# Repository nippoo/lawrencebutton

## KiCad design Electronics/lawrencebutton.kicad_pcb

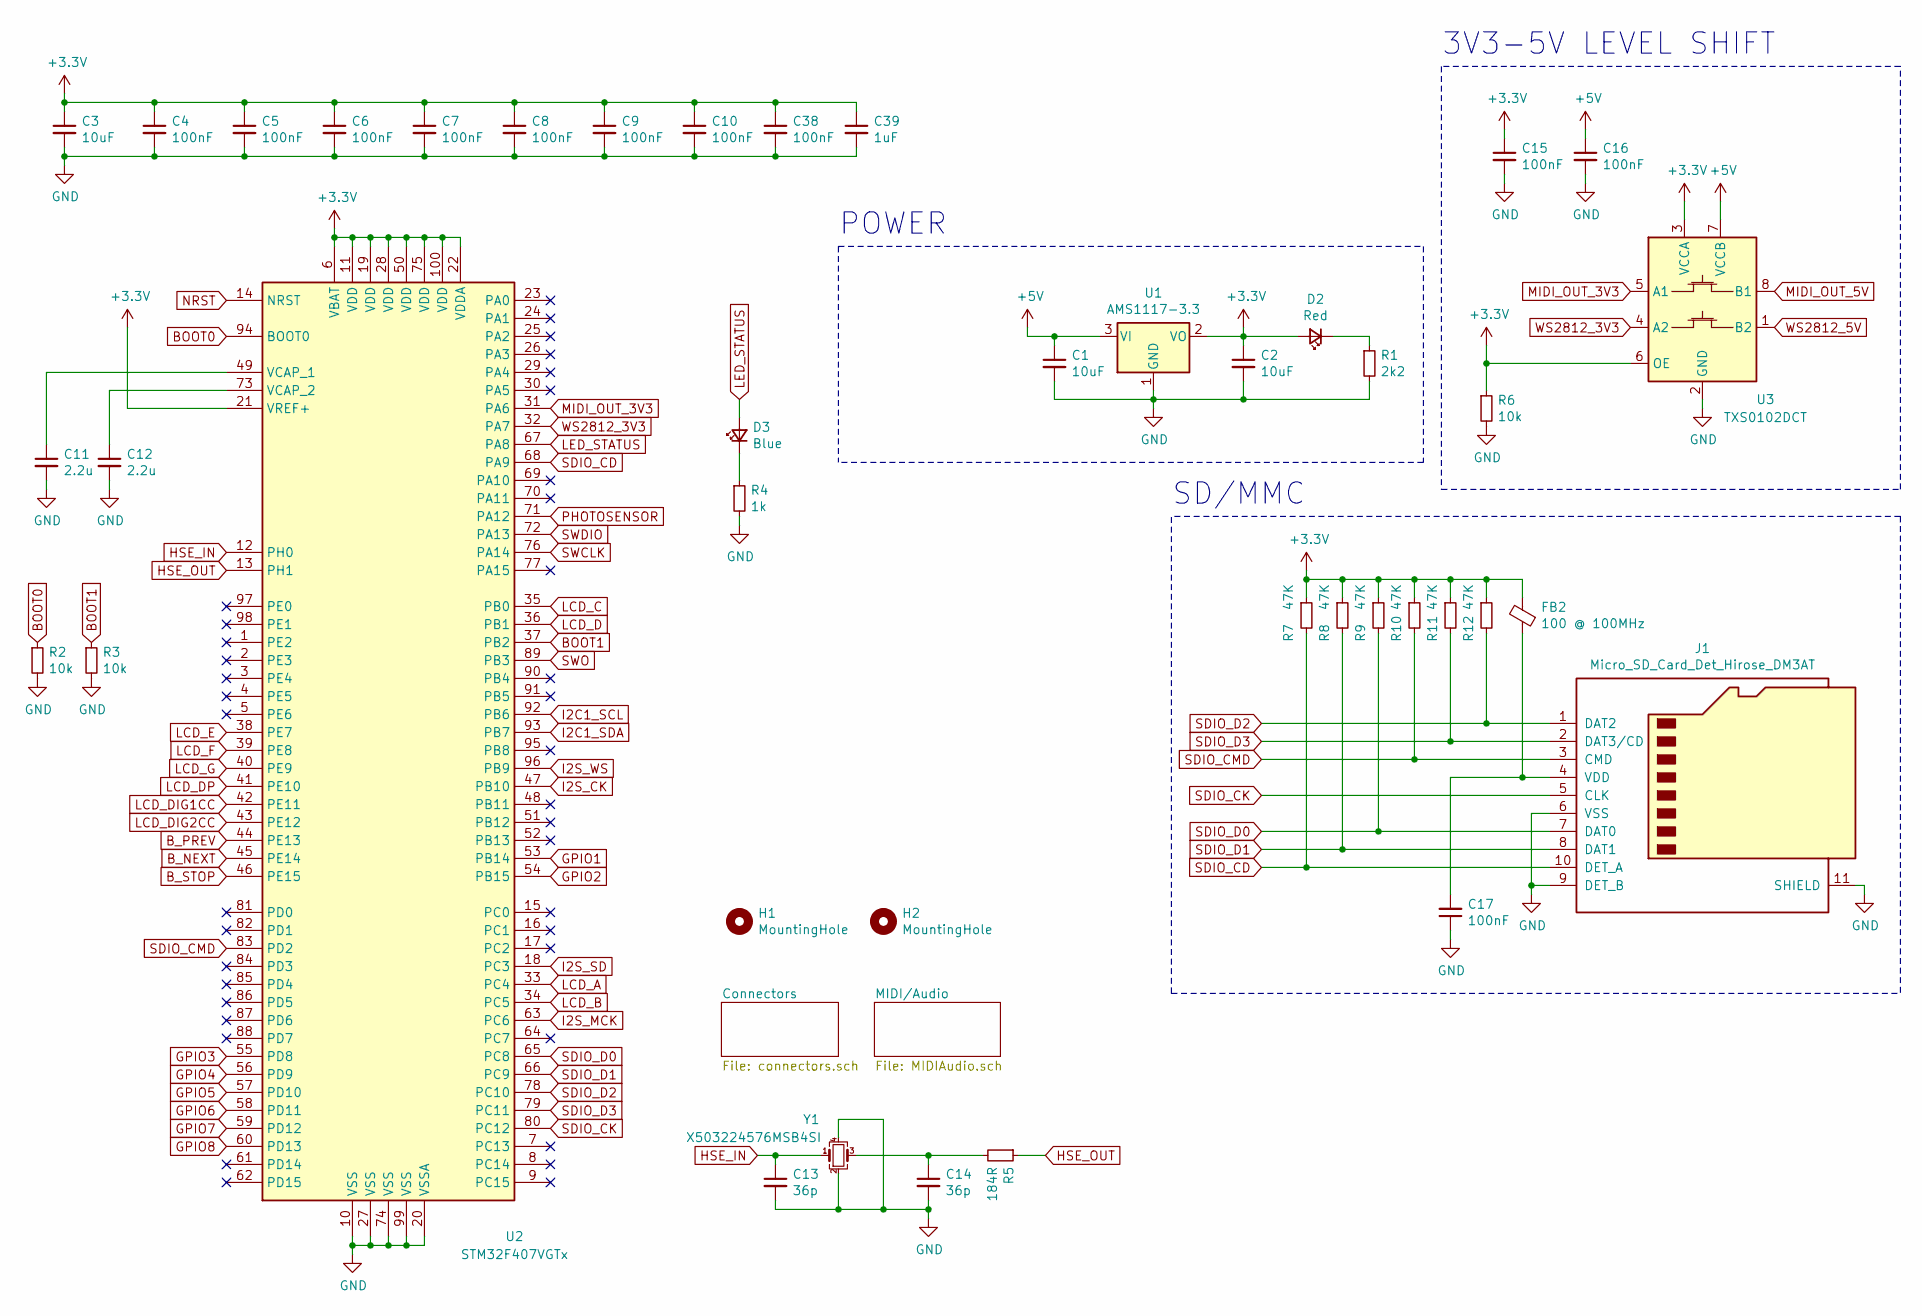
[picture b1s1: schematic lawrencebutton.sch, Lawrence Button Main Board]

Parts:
C1: 10uF; C_0603_1608Metric; LCSC C19702
C2, C3: 10uF; C_0402_1005Metric; LCSC C15525
C4, C5, C6, C7, C8, C9, C10, C15, C16, C17, C38: 100nF; C_0402_1005Metric; LCSC C1525
C11, C12: 2.2u; C_0603_1608Metric; LCSC C23630
C13, C14: 36p; C_0603_1608Metric; LCSC C1663
C39: 1uF; C_0402_1005Metric; LCSC C52923
D2: Red; LED_0805_2012Metric; LCSC C84256
D3: Blue; LED_0805_2012Metric; LCSC C2293
FB2: 100 @ 100MHz; L_0805_2012Metric; LCSC C1015
H1, H2: MountingHole; MountingHole_3.2mm_M3_Pad_Via
J1: Micro_SD_Card_Det_Hirose_DM3AT; microSD_HC_Hirose_DM3AT-SF-PEJM5
R1: 2k2; R_0603_1608Metric; LCSC C4190
R2, R3, R6: 10k; R_0603_1608Metric; LCSC C25804
R4: 1k; R_0603_1608Metric; LCSC C21190
R5: 184R; R_0603_1608Metric; LCSC C22828
R7, R8, R9, R10, R11, R12: 47K; R_0402_1005Metric; LCSC C25792
U1: AMS1117-3.3; SOT-223-3_TabPin2; LCSC C6186
U2: STM32F407VGTx; LQFP-100_14x14mm_P0.5mm; LCSC C12345
U3: TXS0102DCT; SSOP-8_2.95x2.8mm_P0.65mm; LCSC C324082
Y1: X503224576MSB4SI; Crystal_SMD_5032-4Pin_5.0x3.2mm; LCSC C112578

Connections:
+3V3: C2.1, C3.1, C4.1, C5.1, C6.1, C7.1, C8.1, C9.1, C10.1, C15.1, C38.1, C39.1, D2.2 (A), FB2.2, R6.1, R7.1, R8.1, R9.1, R10.1, R11.1, R12.1, U1.2 (VO), U2.6 (VBAT), U2.11 (VDD), U2.19 (VDD), U2.21 (VREF+), U2.22 (VDDA), U2.28 (VDD), U2.50 (VDD), U2.75 (VDD), U2.100 (VDD), U3.3 (VCCA), U3.6 (OE); also elsewhere on the board
+5V: C1.1, C16.1, U1.3 (VI), U3.7 (VCCB); also elsewhere on the board
BOOT0: R2.1, U2.94 (BOOT0)
BOOT1: R3.1, U2.37 (PB2)
B_NEXT: U2.45 (PE14); also elsewhere on the board
B_PREV: U2.44 (PE13); also elsewhere on the board
B_STOP: U2.46 (PE15); also elsewhere on the board
GPIO1: U2.53 (PB14); also elsewhere on the board
GPIO2: U2.54 (PB15); also elsewhere on the board
GPIO3: U2.55 (PD8); also elsewhere on the board
GPIO4: U2.56 (PD9); also elsewhere on the board
GPIO5: U2.57 (PD10); also elsewhere on the board
GPIO6: U2.58 (PD11); also elsewhere on the board
GPIO7: U2.59 (PD12); also elsewhere on the board
GPIO8: U2.60 (PD13); also elsewhere on the board
HSE_IN: C13.1, U2.12 (PH0), Y1.1
HSE_OUT: R5.1, U2.13 (PH1)
I2C1_SCL: U2.92 (PB6); also elsewhere on the board
I2C1_SDA: U2.93 (PB7); also elsewhere on the board
I2S_CK: U2.47 (PB10); also elsewhere on the board
I2S_MCK: U2.63 (PC6); also elsewhere on the board
I2S_SD: U2.18 (PC3); also elsewhere on the board
I2S_WS: U2.96 (PB9); also elsewhere on the board
LCD_A: U2.33 (PC4); also elsewhere on the board
LCD_B: U2.34 (PC5); also elsewhere on the board
LCD_C: U2.35 (PB0); also elsewhere on the board
LCD_D: U2.36 (PB1); also elsewhere on the board
LCD_DIG1CC: U2.42 (PE11); also elsewhere on the board
LCD_DIG2CC: U2.43 (PE12); also elsewhere on the board
LCD_DP: U2.41 (PE10); also elsewhere on the board
LCD_E: U2.38 (PE7); also elsewhere on the board
LCD_F: U2.39 (PE8); also elsewhere on the board
LCD_G: U2.40 (PE9); also elsewhere on the board
LED_STATUS: D3.2 (A), U2.67 (PA8)
MIDI_OUT_3V3: U2.31 (PA6), U3.5 (A1)
MIDI_OUT_5V: U3.8 (B1); also elsewhere on the board
unnamed: C11.1, U2.49 (VCAP_1)
unnamed: C12.1, U2.73 (VCAP_2)
unnamed: C14.1, R5.2, Y1.3
unnamed: C17.2, FB2.1, J1.4 (VDD)
unnamed: D2.1 (K), R1.1
unnamed: D3.1 (K), R4.1
PHOTOSENSOR: U2.71 (PA12); also elsewhere on the board
SDIO_CD: J1.10 (DET_A), R7.2, U2.68 (PA9)
SDIO_CK: J1.5 (CLK), U2.80 (PC12)
SDIO_CMD: J1.3 (CMD), R10.2, U2.83 (PD2)
SDIO_D0: J1.7 (DAT0), R9.2, U2.65 (PC8)
SDIO_D1: J1.8 (DAT1), R8.2, U2.66 (PC9)
SDIO_D2: J1.1 (DAT2), R12.2, U2.78 (PC10)
SDIO_D3: J1.2 (DAT3/CD), R11.2, U2.79 (PC11)
SWCLK: U2.76 (PA14); also elsewhere on the board
SWDIO: U2.72 (PA13); also elsewhere on the board
SWO: U2.89 (PB3); also elsewhere on the board
WS2812_3V3: U2.32 (PA7), U3.4 (A2)
WS2812_5V: U3.1 (B2); also elsewhere on the board

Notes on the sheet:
SD/MMC
POWER
3V3-5V LEVEL SHIFT

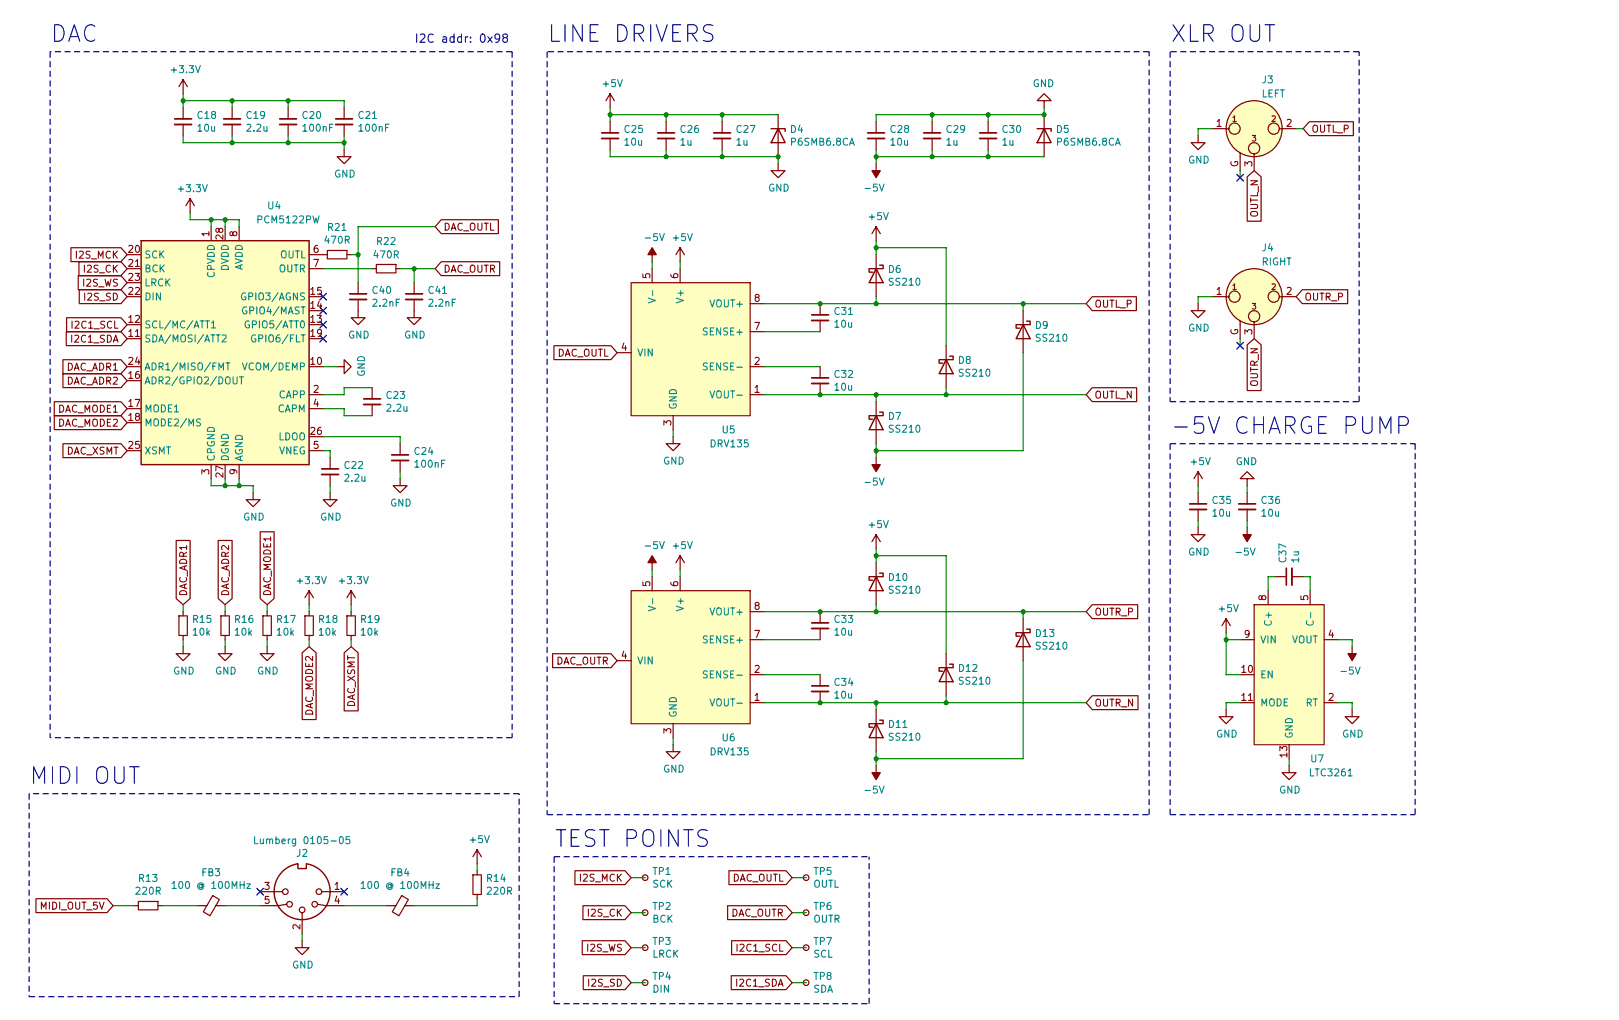
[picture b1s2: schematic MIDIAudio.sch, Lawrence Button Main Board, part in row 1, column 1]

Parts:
C18: 10u; C_0402_1005Metric; LCSC C15525
C19, C22, C23: 2.2u; C_0603_1608Metric; LCSC C23630
C20, C21, C24: 100nF; C_0402_1005Metric; LCSC C1525
C25, C28, C31, C32, C33, C34, C35, C36: 10u; C_0603_1608Metric; LCSC C19702
C26, C27, C29, C30, C37: 1u; C_0402_1005Metric; LCSC C52923
C40, C41: 2.2nF; C_0402_1005Metric; LCSC C1531
D4, D5: P6SMB6.8CA; D_SMB; LCSC C78395
D6, D7, D8, D9, D10, D11, D12, D13: SS210; D_SMA; LCSC C14996
FB3, FB4: 100 @ 100MHz; L_0805_2012Metric; LCSC C1015
J2: Lumberg 0105-05; Lumberg-0105-05
J3: LEFT; Jack_XLR_Neutrik_NC3MAH_Horizontal
J4: RIGHT; Jack_XLR_Neutrik_NC3MAH_Horizontal
R13, R14: 220R; R_0603_1608Metric; LCSC C22962
R15, R16, R17, R18, R19: 10k; R_0603_1608Metric; LCSC C25804
R21, R22: 470R; R_0402_1005Metric; LCSC C25117
TP1: SCK; TestPoint_Loop_D2.50mm_Drill1.0mm
TP2: BCK; TestPoint_Loop_D2.50mm_Drill1.0mm
TP3: LRCK; TestPoint_Loop_D2.50mm_Drill1.0mm
TP4: DIN; TestPoint_Loop_D2.50mm_Drill1.0mm
TP5: OUTL; TestPoint_Loop_D2.50mm_Drill1.0mm
TP6: OUTR; TestPoint_Loop_D2.50mm_Drill1.0mm
TP7: SCL; TestPoint_Loop_D2.50mm_Drill1.0mm
TP8: SDA; TestPoint_Loop_D2.50mm_Drill1.0mm
U4: PCM5122PW; TSSOP-28_4.4x9.7mm_P0.65mm
U5, U6: DRV135; SOIC-8_3.9x4.9mm_P1.27mm
U7: LTC3261; MSOP-12-1EP_3x4mm_P0.65mm_EP1.65x2.85mm_ThermalVias

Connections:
+3V3: C18.1, C19.1, C20.1, C21.1, R18.1, R19.1, U4.1 (CPVDD), U4.8 (AVDD), U4.28 (DVDD); also elsewhere on the board
+5V: C25.1, C26.1, C27.1, C35.1, D4.1 (K), D6.1 (K), D8.1 (K), D10.1 (K), D12.1 (K), R14.1, U5.6 (V+), U6.6 (V+), U7.9 (VIN), U7.10 (EN); also elsewhere on the board
-5V: C28.2, C29.2, C30.2, C36.2, D5.2 (A), D7.2 (A), D9.2 (A), D11.2 (A), D13.2 (A), U5.5 (V-), U6.5 (V-), U7.4 (VOUT)
DAC_ADR1: R15.1, U4.24 (ADR1/MISO/FMT)
DAC_ADR2: R16.1, U4.16 (ADR2/GPIO2/DOUT)
DAC_MODE1: R17.1, U4.17 (MODE1)
DAC_MODE2: R18.2, U4.18 (MODE2/MS)
DAC_OUTL: C40.1, R21.1, TP5.1, U5.4 (VIN)
DAC_OUTR: C41.1, R22.1, TP6.1, U6.4 (VIN)
DAC_XSMT: R19.2, U4.25 (XSMT)
I2C1_SCL: TP7.1, U4.12 (SCL/MC/ATT1); also elsewhere on the board
I2C1_SDA: TP8.1, U4.11 (SDA/MOSI/ATT2); also elsewhere on the board
I2S_CK: TP2.1, U4.21 (BCK); also elsewhere on the board
I2S_MCK: TP1.1, U4.20 (SCK); also elsewhere on the board
I2S_SD: TP4.1, U4.22 (DIN); also elsewhere on the board
I2S_WS: TP3.1, U4.23 (LRCK); also elsewhere on the board
MIDI_OUT_5V: R13.2; also elsewhere on the board
unnamed: C22.1, U4.5 (VNEG)
unnamed: C23.1, U4.2 (CAPP)
unnamed: C23.2, U4.4 (CAPM)
unnamed: C24.1, U4.26 (LDOO)
unnamed: C31.2, U5.7 (SENSE+)
unnamed: C32.1, U5.2 (SENSE-)
unnamed: C33.2, U6.7 (SENSE+)
unnamed: C34.1, U6.2 (SENSE-)
unnamed: C37.1, U7.8 (C+)
unnamed: C37.2, U7.5 (C-)
unnamed: FB3.1, J2.5
unnamed: FB3.2, R13.1
unnamed: FB4.1, R14.2
unnamed: FB4.2, J2.4
unnamed: R21.2, U4.6 (OUTL)
unnamed: R22.2, U4.7 (OUTR)
OUTL_N: C32.2, D7.1 (K), D8.2 (A), J3.3, U5.1 (VOUT-)
OUTL_P: C31.1, D6.2 (A), D9.1 (K), J3.2, U5.8 (VOUT+)
OUTR_N: C34.2, D11.1 (K), D12.2 (A), J4.3, U6.1 (VOUT-)
OUTR_P: C33.1, D10.2 (A), D13.1 (K), J4.2, U6.8 (VOUT+)

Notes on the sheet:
XLR OUT
LINE DRIVERS
DAC
MIDI OUT
I2C addr: 0x98
-5V CHARGE PUMP
TEST POINTS

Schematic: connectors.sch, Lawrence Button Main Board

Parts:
J6: SWD; PinSocket_2x05_P1.27mm_Vertical_SMD
J7: DB; Molex_PicoBlade_53048-1510_1x15_P1.25mm_Horizontal
J8: LEDs; Molex_PicoBlade_53048-0310_1x03_P1.25mm_Horizontal
J9: PHOTOSENSOR; Molex_PicoBlade_53048-0310_1x03_P1.25mm_Horizontal
J11: DBPOWER; Molex_PicoBlade_53048-0310_1x03_P1.25mm_Horizontal
J12: GPIO; PinHeader_1x11_P2.54mm_Vertical
R20: 1k; R_0603_1608Metric

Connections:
+3V3: J6.1, J11.2, J12.10; also elsewhere on the board
+5V: J8.1, J9.1, J12.9; also elsewhere on the board
B_NEXT: J7.12; also elsewhere on the board
B_PREV: J7.11; also elsewhere on the board
B_STOP: J7.13; also elsewhere on the board
GPIO1: J12.1; also elsewhere on the board
GPIO2: J12.2; also elsewhere on the board
GPIO3: J12.3; also elsewhere on the board
GPIO4: J12.4; also elsewhere on the board
GPIO5: J12.5; also elsewhere on the board
GPIO6: J12.6; also elsewhere on the board
GPIO7: J12.7; also elsewhere on the board
GPIO8: J12.8; also elsewhere on the board
LCD_A: J7.1; also elsewhere on the board
LCD_B: J7.2; also elsewhere on the board
LCD_C: J7.3; also elsewhere on the board
LCD_D: J7.4; also elsewhere on the board
LCD_DIG1CC: J7.9; also elsewhere on the board
LCD_DIG2CC: J7.10; also elsewhere on the board
LCD_DP: J7.8; also elsewhere on the board
LCD_E: J7.5; also elsewhere on the board
LCD_F: J7.6; also elsewhere on the board
LCD_G: J7.7; also elsewhere on the board
unnamed: J9.2, R20.1
PHOTOSENSOR: R20.2; also elsewhere on the board
SWCLK: J6.4; also elsewhere on the board
SWDIO: J6.2; also elsewhere on the board
SWO: J6.6; also elsewhere on the board
WS2812_5V: J8.2; also elsewhere on the board

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
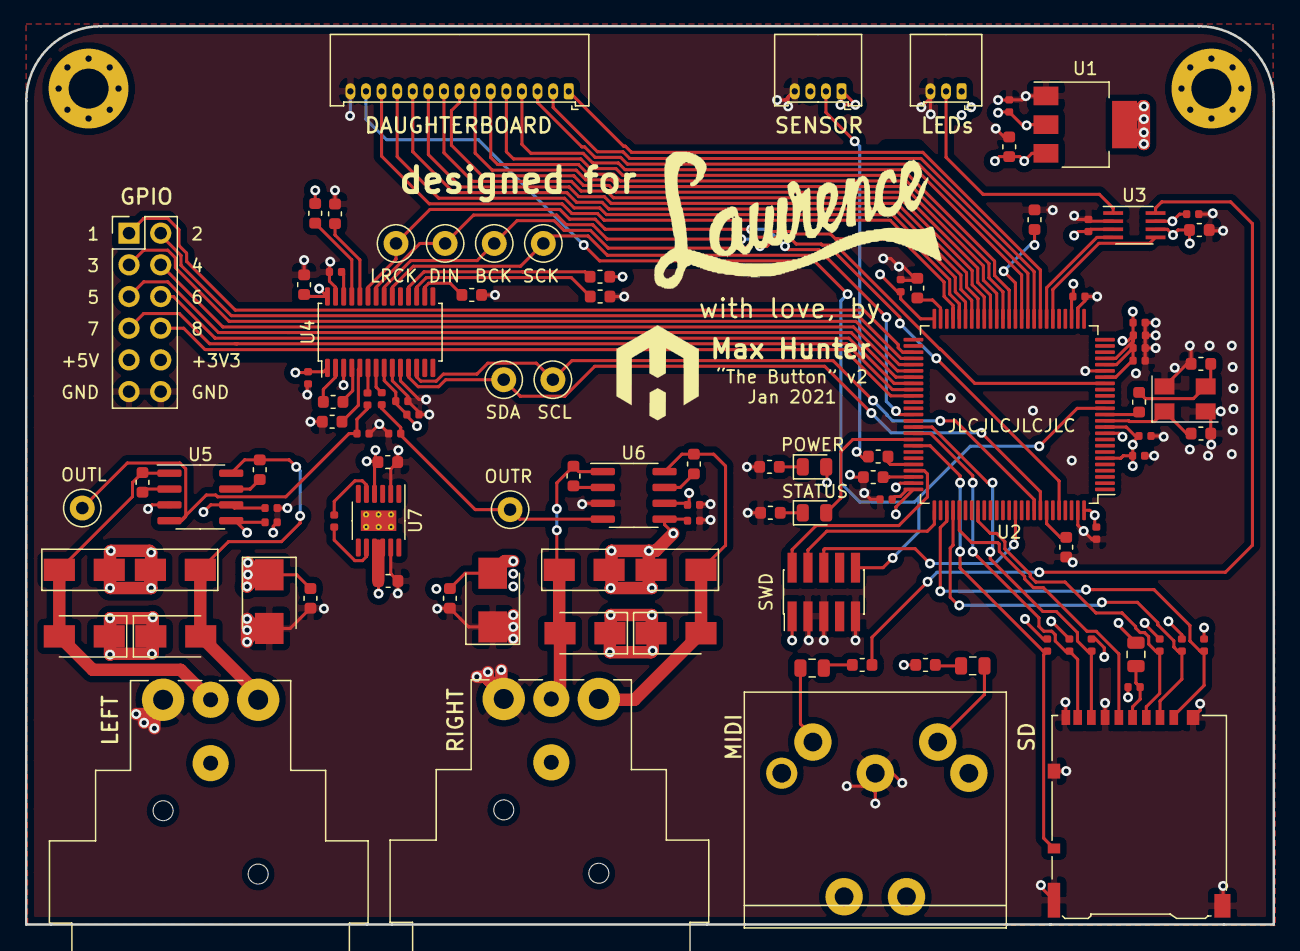
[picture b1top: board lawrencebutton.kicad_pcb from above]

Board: 4 copper layers, 100.0 x 72.0 mm, 105 parts (0 on the bottom side), 86 nets.

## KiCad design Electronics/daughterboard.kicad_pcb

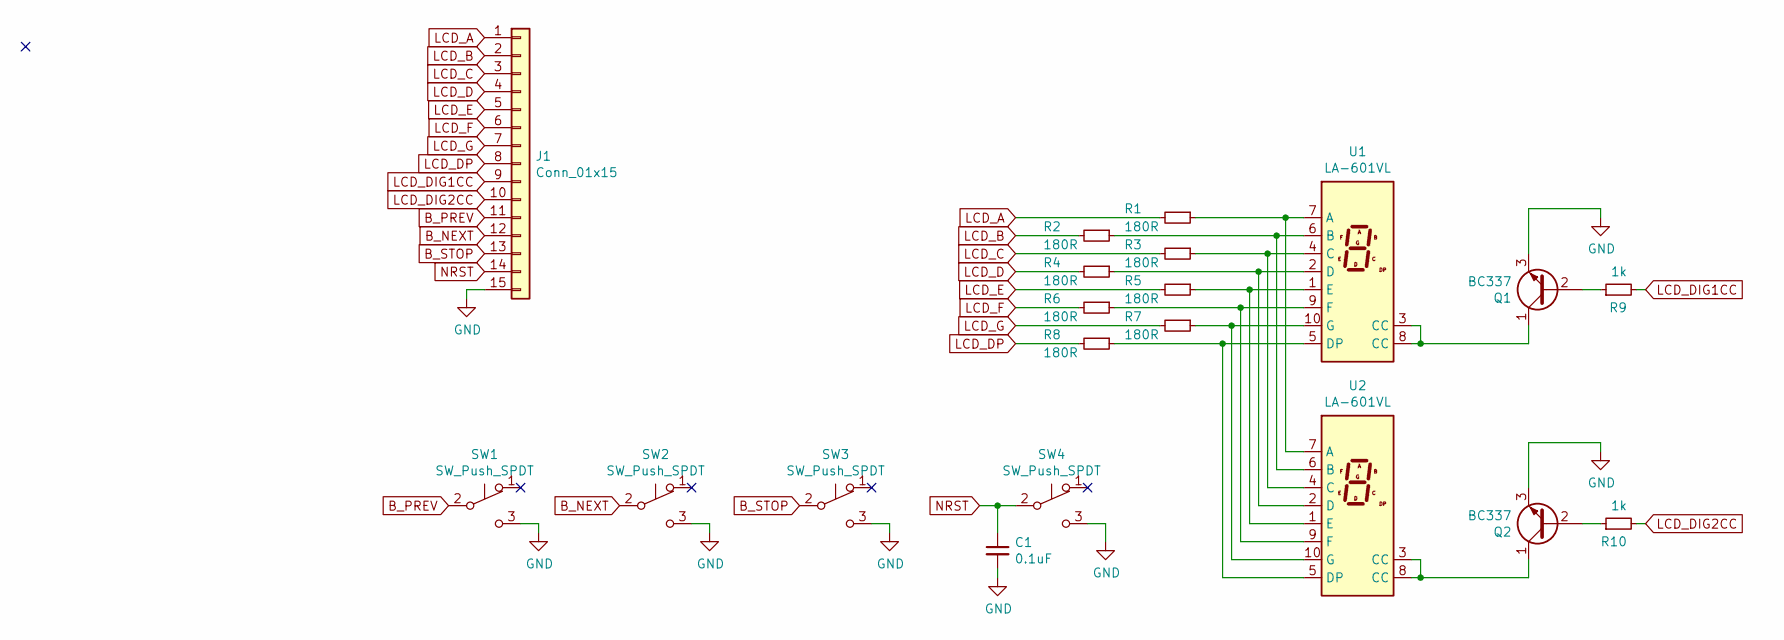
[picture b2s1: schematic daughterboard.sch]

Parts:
C1: 0.1uF; C_Disc_D3.8mm_W2.6mm_P2.50mm
J1: Conn_01x15; Molex_PicoBlade_53048-1510_1x15_P1.25mm_Horizontal
Q1, Q2: BC337; TO-92_Inline
R1, R2, R3, R4, R5, R6, R7, R8: 180R; R_Axial_DIN0207_L6.3mm_D2.5mm_P7.62mm_Horizontal
R9, R10: 1k; R_Axial_DIN0207_L6.3mm_D2.5mm_P7.62mm_Horizontal
SW1, SW2, SW3, SW4: SW_Push_SPDT; SPDT Push Switch RS 734-6788
U1, U2: LA-601VL; 7SegmentLED_LTS6760_LTS6780

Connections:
B_NEXT: J1.12, SW2.2 (B)
B_PREV: J1.11, SW1.2 (B)
B_STOP: J1.13, SW3.2 (B)
GND: C1.2, J1.15, Q1.3 (E), Q2.3 (E), SW1.3 (C), SW2.3 (C), SW3.3 (C), SW4.3 (C)
LCD_A: J1.1, R1.2
LCD_B: J1.2, R2.2
LCD_C: J1.3, R3.2
LCD_D: J1.4, R4.2
LCD_DIG1CC: J1.9, R9.2
LCD_DIG2CC: J1.10, R10.2
LCD_DP: J1.8, R8.2
LCD_E: J1.5, R5.2
LCD_F: J1.6, R6.2
LCD_G: J1.7, R7.2
NRST: C1.1, J1.14, SW4.2 (B)
unnamed: Q1.1 (C), U1.3 (CC), U1.8 (CC)
unnamed: Q1.2 (B), R9.1
unnamed: Q2.1 (C), U2.3 (CC), U2.8 (CC)
unnamed: Q2.2 (B), R10.1
unnamed: R1.1, U1.7 (A), U2.7 (A)
unnamed: R2.1, U1.6 (B), U2.6 (B)
unnamed: R3.1, U1.4 (C), U2.4 (C)
unnamed: R4.1, U1.2 (D), U2.2 (D)
unnamed: R5.1, U1.1 (E), U2.1 (E)
unnamed: R6.1, U1.9 (F), U2.9 (F)
unnamed: R7.1, U1.10 (G), U2.10 (G)
unnamed: R8.1, U1.5 (DP), U2.5 (DP)

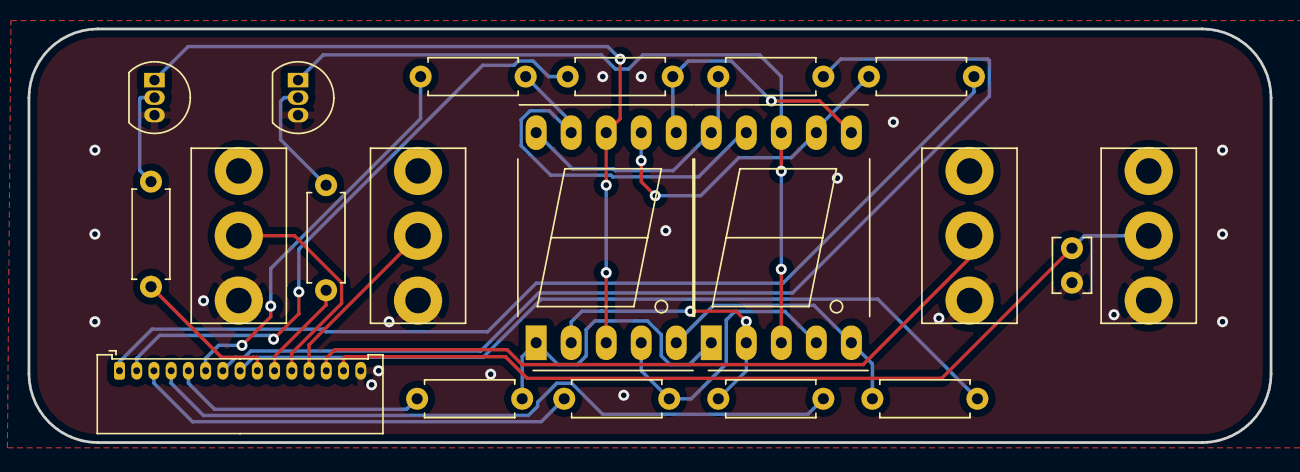
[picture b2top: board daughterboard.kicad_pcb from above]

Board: 2 copper layers, 90.1 x 30.0 mm, 20 parts (0 on the bottom side), 27 nets.

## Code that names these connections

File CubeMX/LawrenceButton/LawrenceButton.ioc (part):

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PC3.Mode=Half_Duplex_Master
PD12.GPIO_Label=GPIO7
PH0-OSC_IN.Signal=RCC_OSC_IN
Mcu.UserName=STM32F407VGTx
PE11.GPIOParameters=GPIO_Label
PD9.GPIOParameters=GPIO_Label
PB10.Mode=Half_Duplex_Master
PE11.GPIO_Label=LCD_DIG1CC
PC10.Signal=SDIO_D2
PC12.Signal=SDIO_CK
PB14.GPIO_Label=GPIO1
PA12.GPIOParameters=GPIO_PuPd,GPIO_Label
PA9.GPIOParameters=GPIO_Label
PB0.GPIO_Label=LCD_C
PA6.GPIO_Label=MIDI_OUT
PB15.Signal=GPIO_Output
RCC.SYSCLKSource=RCC_SYSCLKSOURCE_PLLCLK
PD13.Signal=GPIO_Output
PA12.Signal=GPXTI12
PD11.GPIO_Label=GPIO6
PB6.Signal=I2C1_SCL
PD8.GPIOParameters=GPIO_Label
PB6.Mode=I2C
PC3.Signal=I2S2_SD
PA8.GPIOParameters=GPIO_Label
PD8.Signal=GPIO_Output
PH0-OSC_IN.Mode=HSE-External-Oscillator
PD10.GPIOParameters=GPIO_Label
RCC.HSE_VALUE=24576000
PB3.Mode=Trace_Asynchronous_SW
PE13.GPIO_PuPd=GPIO_PULLUP
PB0.GPIOParameters=GPIO_PuPd,GPIO_Label
PE13.Signal=GPIO_Input
PC4.GPIO_Label=LCD_A
PE9.Signal=GPIO_Output
PA14.Mode=Trace_Asynchronous_SW
PB1.GPIO_Label=LCD_D
PC9.Mode=SD_4_bits_Wide_bus
PB7.Signal=I2C1_SDA
PA8.Signal=GPIO_Output
PE10.Signal=GPIO_Output
PH1-OSC_OUT.Mode=HSE-External-Oscillator
PD13.GPIO_Label=GPIO8
Mcu.Package=LQFP100
PB9.Signal=I2S2_WS
PB1.Signal=GPIO_Output
PA6.Signal=GPIO_Output
PE10.GPIOParameters=GPIO_Label
PD12.Signal=GPIO_Output
PE12.GPIO_Label=LCD_DIG2CC
PC11.Mode=SD_4_bits_Wide_bus
PB14.GPIOParameters=GPIO_Label
PC5.Signal=GPIO_Output
PE7.Signal=GPIO_Output
PA12.GPIO_PuPd=GPIO_PULLUP
PE10.GPIO_Label=LCD_DP
PC4.GPIOParameters=GPIO_Label
PA6.GPIOParameters=GPIO_Label
PE8.GPIOParameters=GPIO_Label
PE14.GPIOParameters=GPIO_PuPd,GPIO_Label
PD9.GPIO_Label=GPIO4
PC11.Signal=SDIO_D3
PA9.GPIO_Label=SDIO_CD
PC8.Signal=SDIO_D0
PC4.Signal=GPIO_Output
PC6.Signal=I2S2_MCK
PC10.Mode=SD_4_bits_Wide_bus
PD13.GPIOParameters=GPIO_Label
PE14.GPIO_Label=B_NEXT
PD9.Signal=GPIO_Output
PA12.GPIO_Label=TRIGGER
PE9.GPIOParameters=GPIO_Label
PE15.GPIOParameters=GPIO_PuPd,GPIO_Label
PD8.GPIO_Label=GPIO3
PD10.Signal=GPIO_Output
PA13.Signal=SYS_JTMS-SWDIO
PA8.GPIO_Label=LED_STATUS
PE15.GPIO_Label=B_STOP
PD12.GPIOParameters=GPIO_Label
PE7.GPIOParameters=GPIO_Label
PC6.Mode=Master_Clock_Activated
PE8.GPIO_Label=LCD_F
PC5.GPIOParameters=GPIO_Label
PB9.Mode=Half_Duplex_Master
PA9.Signal=GPIO_Input
PD10.GPIO_Label=GPIO5
PE11.Signal=GPIO_Output
PE9.GPIO_Label=LCD_G
PA7.GPIO_PuPd=GPIO_PULLDOWN
PB10.Signal=I2S2_CK
PB14.Signal=GPIO_Output
PD2.Mode=SD_4_bits_Wide_bus
PE13.GPIOParameters=GPIO_PuPd,GPIO_Label
PC12.Mode=SD_4_bits_Wide_bus
board=custom
PA7.GPIO_Speed=GPIO_SPEED_FREQ_HIGH
PD11.GPIOParameters=GPIO_Label
PE14.Signal=GPIO_Input
PE15.Signal=GPIO_Input
PB15.GPIO_Label=GPIO2
PE8.Signal=GPIO_Output
PH1-OSC_OUT.Signal=RCC_OSC_OUT
PE14.GPIO_PuPd=GPIO_PULLUP
PB15.GPIOParameters=GPIO_Label
PA13.Mode=Trace_Asynchronous_SW
Mcu.Name=STM32F407V(E-G)Tx
PE7.GPIO_Label=LCD_E
PE12.Signal=GPIO_Output
PC8.Mode=SD_4_bits_Wide_bus
PB3.Signal=SYS_JTDO-SWO
RCC.SYSCLKFreq_VALUE=167936000
PA7.GPIO_Label=WS2812
PE13.GPIO_Label=B_PREV
PC5.GPIO_Label=LCD_B
PD11.Signal=GPIO_Output
PB7.Mode=I2C
PA14.Signal=SYS_JTCK-SWCLK
PE15.GPIO_PuPd=GPIO_PULLUP
PC9.Signal=SDIO_D1
PE12.GPIOParameters=GPIO_Label
PD2.Signal=SDIO_CMD
PB0.Signal=GPIO_Output
PA7.GPIOParameters=GPIO_Speed,GPIO_PuPd,GPIO_Label
PB0.GPIO_PuPd=GPIO_NOPULL
PB1.GPIOParameters=GPIO_Label
PA7.Signal=S_TIM3_CH2

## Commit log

2021-01-16 Initial main board schematic, pre layout
2021-01-17 First layout
2021-02-02 Initial software commit.
2021-02-03 working DMA circular audio buffer
2021-02-03 Initial working WS2812b code
2021-02-05 Refactor, initial commit of first production codebase
2021-02-05 Working LCD count-up/down
2021-02-09 v1 working, fixed red LED pulse
2021-04-08 Swapped RGB -> GRB for hex code LED
2021-04-08 Fixed warnings
